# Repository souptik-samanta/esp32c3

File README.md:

# ESP32-C3 Custom Development Board

A compact, custom-designed ESP32-C3 development board with USB-C connectivity, onboard antenna, and a clean PCB layout.

---

## 3D Render

The board features a USB-C connector on the left side, two tactile switches (BOOT and EN), the ESP32-C3 QFN package at the center-right, a PCB trace antenna on the far right, and a 4-pin UART header (3V3, RXD, TXD, GND) along the bottom edge. All passives are 0402/0603 for a tight layout.
with onboard temp humidity barometer and pressure
---

## PCB Layout

### 3d Render

### Front Copper

### Back Copper

### IN 1

### IN 2

### Board Outline

---

## Features

- **Microcontroller:** ESP32-C3 (RISC-V single-core, up to 160 MHz)
- **Wireless:** 2.4 GHz Wi-Fi 4 and Bluetooth 5 (LE)
- **USB-C:** For power and programming, no external UART adapter needed
- **PCB Antenna:** Integrated trace antenna, no external module required
- **UART Header:** 4-pin breakout (3V3, RXD, TXD, GND) for serial debugging
- **Buttons:** BOOT and EN (reset) tactile switches
- **Power:** USB 5V input with onboard 3.3V regulation
- **Form Factor:** Compact two-layer board, hand-solderable with hot air

---

## Pin Header

| Pin | Function |
|-----|----------|
| 1   | +3V3     |
| 2   | RXD      |
| 3   | TXD      |
| 4   | GND      |

---

## Getting Started

1. Connect the board via USB-C to your computer.
2. Install the [ESP-IDF](https://docs.espressif.com/projects/esp-idf/en/latest/esp32c3/get-started/) toolchain or use the Arduino core for ESP32.
3. Hold the BOOT button while pressing EN to enter download mode.
4. Flash your firmware and hit EN to run.

For serial debugging without USB, wire up the 4-pin UART header to any USB-to-serial adapter at 3.3V logic levels.

## License

Hardware design files are provided as-is. Use at your own risk. Feel free to fork, modify, and build on this design for personal or commercial projects.

To make this 
Please download the esp32.zip(gerber files)
go to jlcpcb upload
upload the BOM AND cpl files and order!!
that simple

# Bill of Materials (BOM)

| Comment | Designator | Footprint | JLCPCB Part # |
|----------|------------|------------|---------------|
| W25Q128JVP | U2 | Winbond_USON-8-2EP_3x4mm_P0.8mm_EP0.2x0.8mm | C2999380 |
| RESET | SW2, SW1 | SW_SPST_TS-1088-xR020 | C778164 |
| 27pF | C1, C2 | 0603 | C1656 |
| 470Ω | R3, R4 | 0402 | C25117 |
| USBLC6-2P6 | U3 | SOT-666 | C15999 |
| 10µF | C14, C15, C3, C7 | 0805 | C440198 |
| 100nF | C4, C5, C6, C8, C9 | 0402 | C1525 |
| 5.1KΩ | R2, R5, R6, R7, R8, R9 | 0402 | C25905 |
| ESP32-C3 | U1 | QFN-32-1EP_5x5mm_P0.5mm_EP3.7x3.7mm | C2838500 |
| 22Ω | R1 | 0402 | C25092 |
| 100nF | C10, C11, C12, C13, C16, C18, C19 | 0603 | C14663 |
| USB_C_Receptacle_USB2.0_14P | J1 | USB_C_Receptacle_HCTL_HC-TYPE-C-16P-01A | C2997432 |
| MS5611-01BA | U4 | LGA-8_3x5mm_P1.25mm | C15639 |
| 2.2µF | C17 | 0603 | C23630 |
| 2.2nH | L1, L2, L3 | 0402 | C6652831 |
| SPX3819M5-L-3-3 | U5 | SOT-23-5 | C20617301 |
| 3.3pF | C20, C21 | 0402 | C1565 |
| Crystal_GND24 | Y2 | Crystal_SMD_3225-4Pin_3.2x2.5mm | C5444549 |
| SHTC3 | U6 | Sensirion_DFN-4-1EP_2x2mm_P1mm_EP0.7x1.6mm | C2880044 |

---

## Cost Breakdown

- PCB Fabrication Cost: **$10 USD**
- Total Cost (Including Shipping): **$~ 162 USD**

# How to use it / assemble it
Go to jlcpcb upload gerber select pcba 
give the cpl and desgnator files
order it
wait 
and there u have it 
connect usb c cable use arduino ide thonny esp32 tool whatever u want lol
---

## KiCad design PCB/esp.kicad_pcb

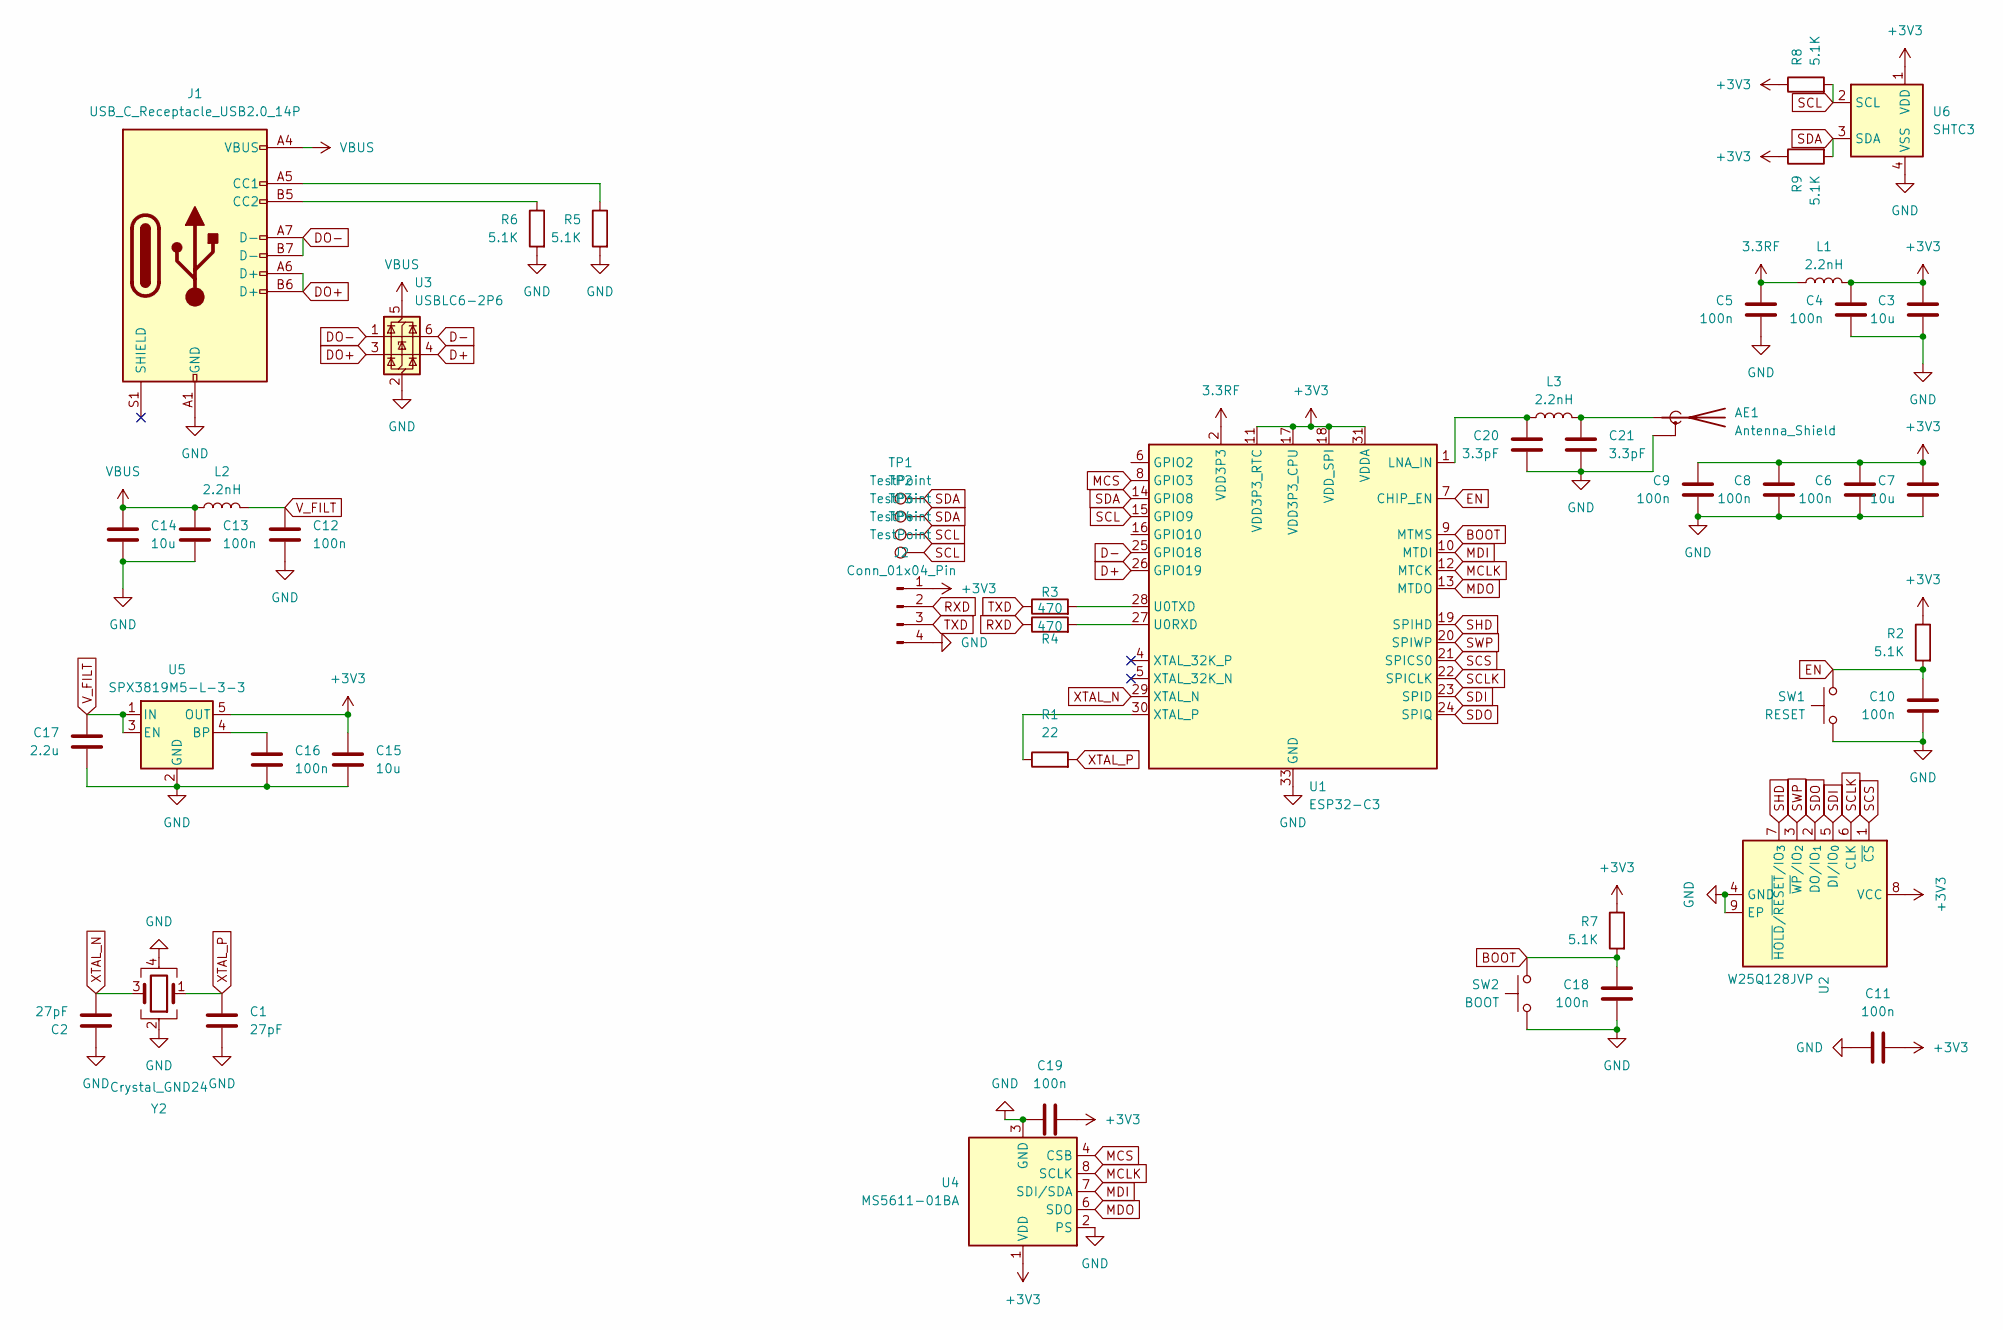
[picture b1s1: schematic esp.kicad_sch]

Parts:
AE1: Antenna_Shield; Texas_SWRA117D_2.4GHz_Left
C1, C2: 27pF; C_0603_1608Metric
C3, C7, C14, C15: 10u; C_0805_2012Metric
C4, C5, C6, C8, C9: 100n; C_0402_1005Metric
C10, C11, C12, C13, C16, C18, C19: 100n; C_0603_1608Metric
C17: 2.2u; C_0603_1608Metric
C20, C21: 3.3pF; C_0402_1005Metric
J1: USB_C_Receptacle_USB2.0_14P; USB_C_Receptacle_HCTL_HC-TYPE-C-16P-01A
J2: Conn_01x04_Pin; PinHeader_1x04_P2.54mm_Vertical
L1, L2, L3: 2.2nH; L_0402_1005Metric
R1: 22; R_0402_1005Metric
R2, R5, R6, R7, R8, R9: 5.1K; R_0402_1005Metric
R3, R4: 470; R_0402_1005Metric
SW1: RESET; SW_SPST_TS-1088-xR020
SW2: BOOT; SW_SPST_TS-1088-xR020
TP1, TP2, TP3, TP4: TestPoint; PinHeader_1x01_P1.00mm_Vertical
U1: ESP32-C3; QFN-32-1EP_5x5mm_P0.5mm_EP3.7x3.7mm
U2: W25Q128JVP; Winbond_USON-8-2EP_3x4mm_P0.8mm_EP0.2x0.8mm
U3: USBLC6-2P6; SOT-666
U4: MS5611-01BA; LGA-8_3x5mm_P1.25mm
U5: SPX3819M5-L-3-3; SOT-23-5
U6: SHTC3; Sensirion_DFN-4-1EP_2x2mm_P1mm_EP0.7x1.6mm
Y2: Crystal_GND24; Crystal_SMD_3225-4Pin_3.2x2.5mm

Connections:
3.3RF: C5.1, L1.2, U1.2 (VDD3P3), U1.3 (VDD3P3)
+3V3: C3.1, C4.1, C6.1, C7.1, C8.1, C9.1, C11.2, C15.1, C19.2, J2.1, L1.1, R2.1, R7.1, R8.1, R9.1, U1.11 (VDD3P3_RTC), U1.17 (VDD3P3_CPU), U1.18 (VDD_SPI), U1.31 (VDDA), U1.32 (VDDA), U2.8 (VCC), U4.1 (VDD), U5.5 (OUT), U6.1 (VDD)
BOOT: C18.1, R7.2, SW2.2, U1.9 (MTMS)
D+: U1.26 (GPIO19), U3.4 (I/O2)
D-: U1.25 (GPIO18), U3.6 (I/O1)
DO+: J1.A6 (D+), J1.B6 (D+), U3.3 (I/O2)
DO-: J1.A7 (D-), J1.B7 (D-), U3.1 (I/O1)
EN: C10.1, R2.2, SW1.2, U1.7 (CHIP_EN)
GND: AE1.2 (Shield), C1.2, C2.1, C3.2, C4.2, C5.2, C6.2, C7.2, C8.2, C9.2, C10.2, C11.1, C12.2, C13.2, C14.2, C15.2, C16.2, C17.2, C18.2, C19.1, C20.2, C21.2, J1.A1 (GND), J1.A12 (GND), J1.B1 (GND), J1.B12 (GND), J2.4, R5.2, R6.2, SW1.1, SW2.1, U1.33 (GND), U2.4 (GND), U2.9 (EP), U3.2 (GND), U4.2 (PS), U4.3 (GND), U5.2 (GND), U6.4 (VSS), Y2.2, Y2.4
MCLK: U1.12 (MTCK), U4.8 (SCLK)
MCS: U1.8 (GPIO3), U4.4 (CSB), U4.5 (CSB)
MDI: U1.10 (MTDI), U4.7 (SDI/SDA)
MDO: U1.13 (MTDO), U4.6 (SDO)
unnamed: AE1.1 (A), C21.1, L3.1
unnamed: J1.A5 (CC1), R5.1
unnamed: J1.B5 (CC2), R6.1
unnamed: C20.1, L3.2, U1.1 (LNA_IN)
unnamed: R4.2, U1.27 (U0RXD)
unnamed: R3.2, U1.28 (U0TXD)
unnamed: R1.1, U1.30 (XTAL_P)
unnamed: C16.1, U5.4 (BP)
RXD: J2.2, R4.1
SCL: R8.2, TP3.1, TP4.1, U1.15 (GPIO9), U6.2 (SCL)
SCLK: U1.22 (SPICLK), U2.6 (CLK)
SCS: U1.21 (SPICS0), U2.1 (~CS)
SDA: R9.2, TP1.1, TP2.1, U1.14 (GPIO8), U6.3 (SDA)
SDI: U1.23 (SPID), U2.5 (DI/IO_{0})
SDO: U1.24 (SPIQ), U2.2 (DO/IO_{1})
SHD: U1.19 (SPIHD), U2.7 (~HOLD/~RESET/IO_{3})
SWP: U1.20 (SPIWP), U2.3 (~WP/IO_{2})
TXD: J2.3, R3.1
VBUS: C13.1, C14.1, J1.A4 (VBUS), J1.A9 (VBUS), J1.B4 (VBUS), J1.B9 (VBUS), L2.1, U3.5 (VBUS)
V_FILT: C12.1, C17.1, L2.2, U5.1 (IN), U5.3 (EN)
XTAL_N: C2.2, U1.29 (XTAL_N), Y2.3
XTAL_P: C1.1, R1.2, Y2.1

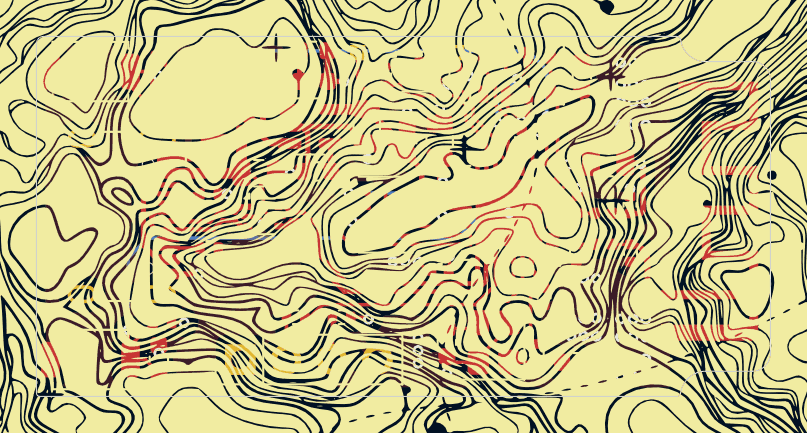
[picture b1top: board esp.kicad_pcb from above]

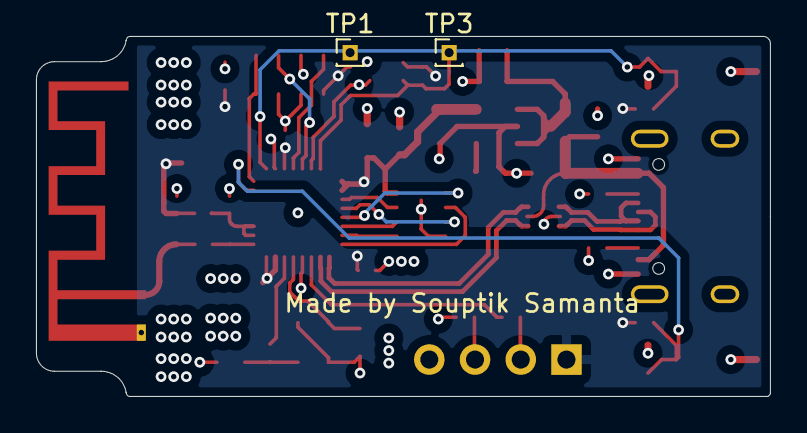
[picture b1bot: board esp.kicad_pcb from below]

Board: 4 copper layers, 40.8 x 20.0 mm, 48 parts (2 on the bottom side), 35 nets.

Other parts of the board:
.: LOGO

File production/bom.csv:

Designator,Footprint,Quantity,Value,LCSC Part #
AE1,Texas_SWRA117D_2.4GHz_Left,1,Antenna_Shield,
"C1, C2",0603,2,27pF,
"C10, C11, C12, C13, C16, C18, C19",0603,7,100n,
"C14, C15, C3, C7",0805,4,10u,
C17,0603,1,2.2u,
"C20, C21",0402,2,3.3pF,
"C4, C5, C6, C8, C9",0402,5,100n,
J1,USB_C_Receptacle_HCTL_HC-TYPE-C-16P-01A,1,USB_C_Receptacle_USB2.0_14P,
J2,PinHeader_1x04_P2.54mm_Vertical,1,Conn_01x04_Pin,
"L1, L2, L3",0402,3,2.2nH,
R1,0402,1,22,
"R2, R5, R6, R7, R8, R9",0402,6,5.1K,
"R3, R4",0402,2,470,
SW1,SW_SPST_TS-1088-xR020,1,RESET,
SW2,SW_SPST_TS-1088-xR020,1,BOOT,
U1,QFN-32-1EP_5x5mm_P0.5mm_EP3.7x3.7mm,1,ESP32-C3,
U2,Winbond_USON-8-2EP_3x4mm_P0.8mm_EP0.2x0.8mm,1,W25Q128JVP,
U3,SOT-666,1,USBLC6-2P6,
U4,LGA-8_3x5mm_P1.25mm,1,MS5611-01BA,
U5,SOT-23-5,1,SPX3819M5-L-3-3,
U6,Sensirion_DFN-4-1EP_2x2mm_P1mm_EP0.7x1.6mm,1,SHTC3,
Y2,Crystal_SMD_3225-4Pin_3.2x2.5mm,1,Crystal_GND24,

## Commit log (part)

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2026-02-27 eyeyey
2026-03-04 pushing before redoing everything
2026-03-04 Add BOM and Cost Breakdown to README
    Added Bill of Materials (BOM) and Cost Breakdown sections to the README.
2026-03-16 Assembly plan added
